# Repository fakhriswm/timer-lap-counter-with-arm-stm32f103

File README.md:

# timer-lap-counter-with-arm-stm32f103
Project sistem Embeddded menghitung lap dan timer yang menggunakan stm32 f103
Project ini dibuat untuk memenuhi UTS semester ganjil 3 D4 elektronika B PENS

didalam project ini berisi :
1. Source code
2. File schematic .sch
3. File board .brd

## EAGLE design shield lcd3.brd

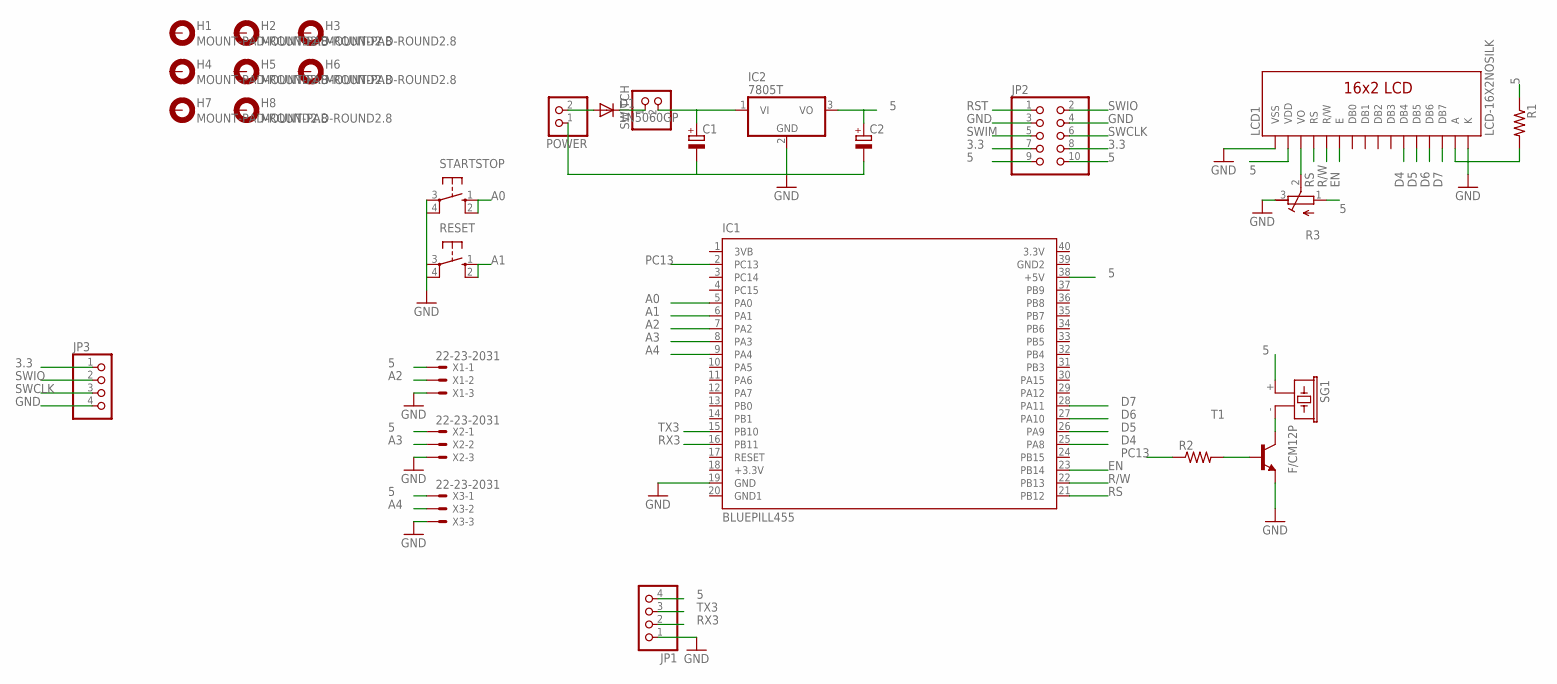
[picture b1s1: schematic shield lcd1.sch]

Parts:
C1: CPOL-EUE2.5-7; E2,5-7
C2: CPOL-EUE2.5-6; E2,5-6
D1: 1N5060GP; DO15-12
H1, H2, H3, H4, H5, H6, H7, H8: MOUNT-PAD-ROUND2.8; 2,8-PAD
IC1: BLUEPILL455; DIL40
IC2: 7805T; TO220H
JP1, JP3: PINHD-1X4; 1X04
JP2: PINHD-2X5; 2X05
LCD1: LCD-16X2NOSILK; LCD-16X2_NOSILK
POWER: PINHD-1X2; 1X02
R1: R-US_0207/10; 0207/10
R2: R-US_M0805; M0805
R3: R-TRIMM3339P; RTRIM3339P
RESET: 40-XX; B3F-40XX
SG1: F/CM12P
STARTSTOP: 40-XX; B3F-40XX
SWITCH: PINHD-1X2; 1X02
T1: BF820-NPN-SOT23-BEC; SOT23-BEC
X1, X2, X3: 22-23-2031

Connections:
3.3: JP2.7, JP2.8, JP3.1
5: C2.+, IC1.38 (+5V), IC2.3 (VO), JP1.4, JP2.9, JP2.10, LCD1.2 (VDD), R1.1, R3.1 (A), SG1.+ (1), X1.1, X2.1, X3.1
A0: IC1.5 (PA0), STARTSTOP.1 (S), STARTSTOP.2 (S1)
A1: IC1.6 (PA1), RESET.1 (S), RESET.2 (S1)
A2: IC1.7 (PA2), X1.2
A3: IC1.8 (PA3), X2.2
A4: IC1.9 (PA4), X3.2
D4: IC1.25 (PA8), LCD1.11 (DB4)
D5: IC1.26 (PA9), LCD1.12 (DB5)
D6: IC1.27 (PA10), LCD1.13 (DB6)
D7: IC1.28 (PA11), LCD1.14 (DB7)
EN: IC1.23 (PB14), LCD1.6 (E)
GND: C1.-, C2.-, IC1.19 (GND), IC2.2 (GND), JP1.1, JP2.3, JP2.4, JP3.4, LCD1.1 (VSS), LCD1.16 (K), POWER.1, R3.3 (E), RESET.3, RESET.4 (P1), STARTSTOP.3, STARTSTOP.4 (P1), T1.E, X1.3, X2.3, X3.3
unnamed: LCD1.15 (A), R1.2
unnamed: R2.2, T1.B
unnamed: C1.+, IC2.1 (VI), SWITCH.2
unnamed: SG1.- (2), T1.C
unnamed: LCD1.3 (VO), R3.2 (S)
unnamed: D1.C, SWITCH.1
unnamed: D1.A, POWER.2
PA6: IC1.11 (PA6)
PA7: IC1.12 (PA7)
PB3: IC1.31 (PB3)
PB4: IC1.32 (PB4)
PC13: IC1.2 (PC13), R2.1
R/W: IC1.22 (PB13), LCD1.5 (R/W)
RS: IC1.21 (PB12), LCD1.4 (RS)
RST: JP2.1
RX3: IC1.16 (PB11), JP1.2
SWCLK: JP2.6, JP3.3
SWIM: JP2.5
SWIO: JP2.2, JP3.2
TX3: IC1.15 (PB10), JP1.3

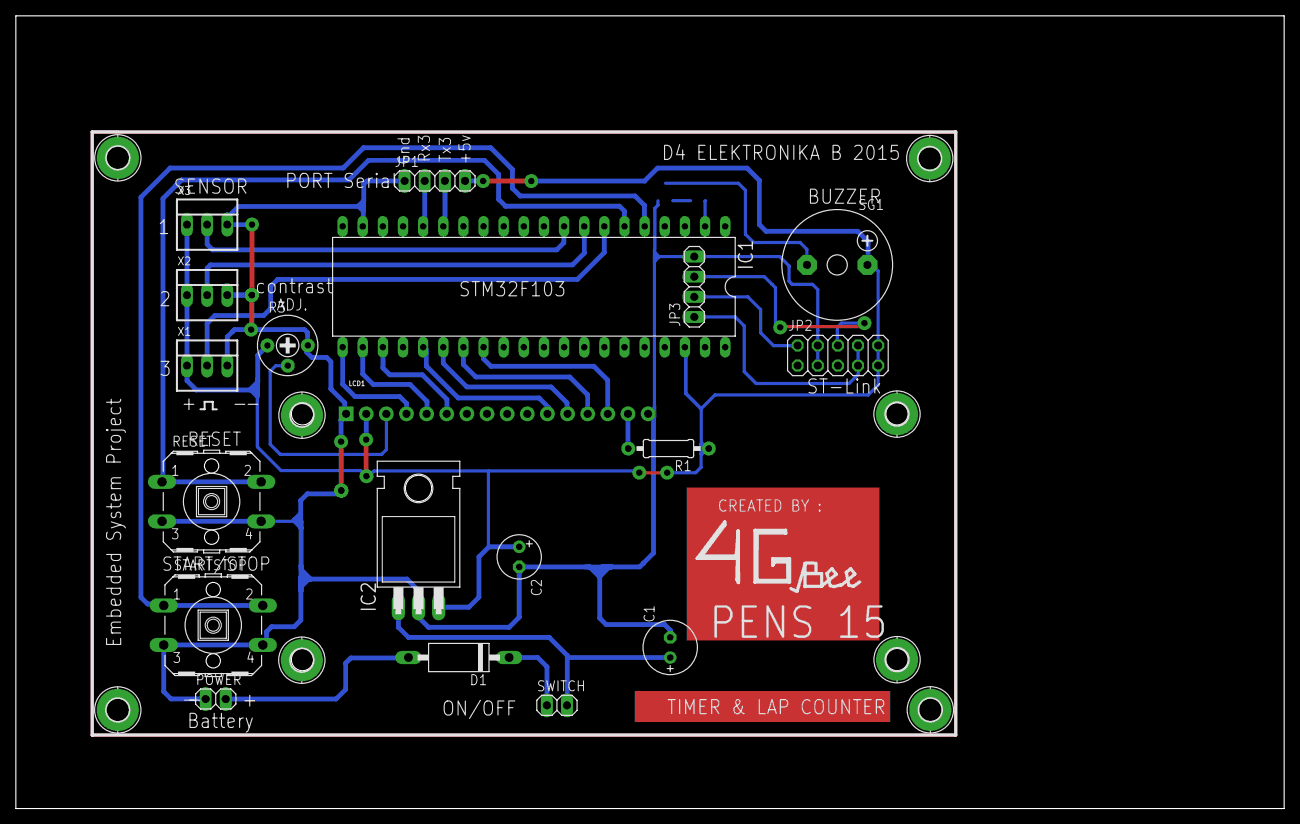
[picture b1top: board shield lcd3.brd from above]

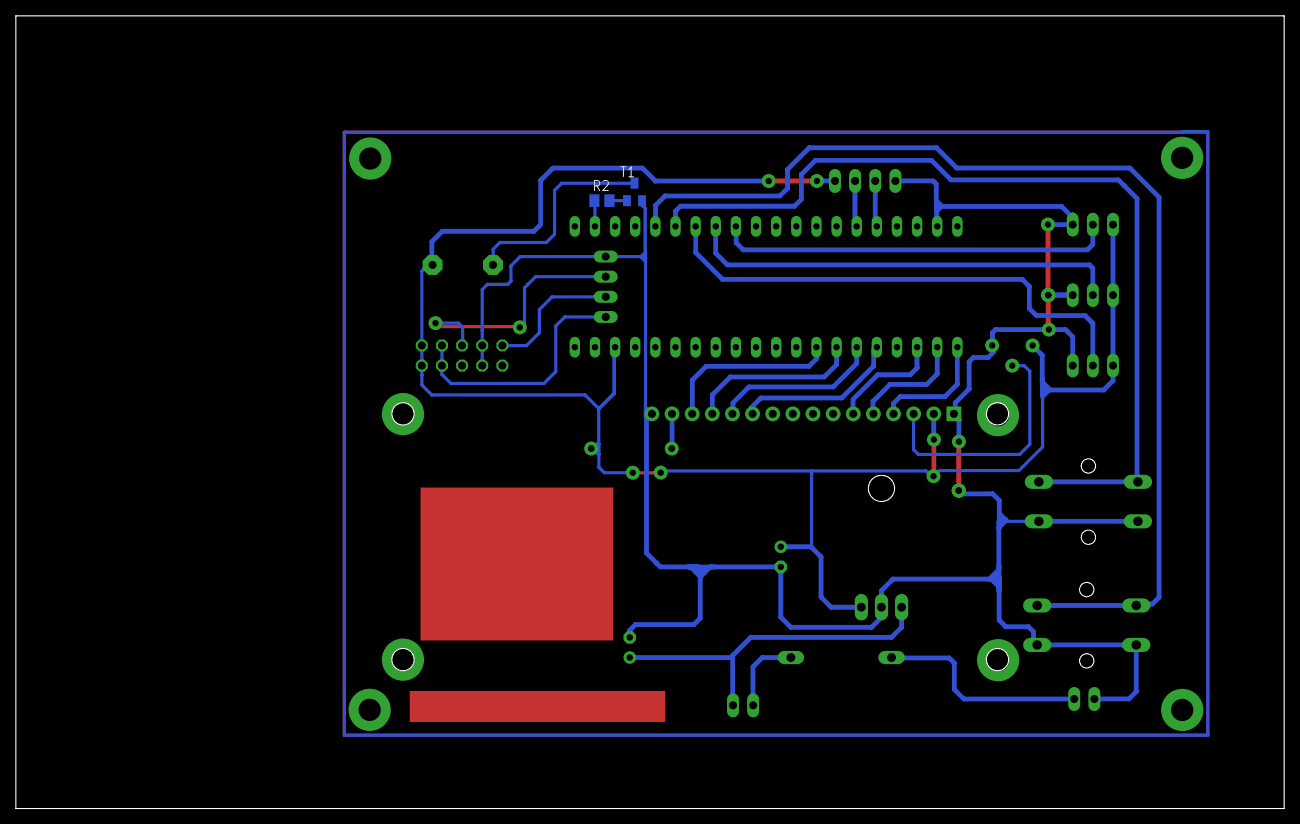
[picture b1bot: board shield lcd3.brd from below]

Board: 2 copper layers, 160.0 x 100.0 mm, 29 parts (2 on the bottom side), 27 nets.

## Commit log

2017-11-20 Readme
2017-11-20 file schematic rangkaian Shield IO
2017-11-20 board Eagle rangkaian Shield IO

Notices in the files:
parts and their libraries:
SparkFun-Displays: Licensing: Creative Commons ShareAlike 4.0 International - https://creativecommons.org/licenses/by-sa/4.0
